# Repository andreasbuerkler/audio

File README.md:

# audio
audio signal processing board

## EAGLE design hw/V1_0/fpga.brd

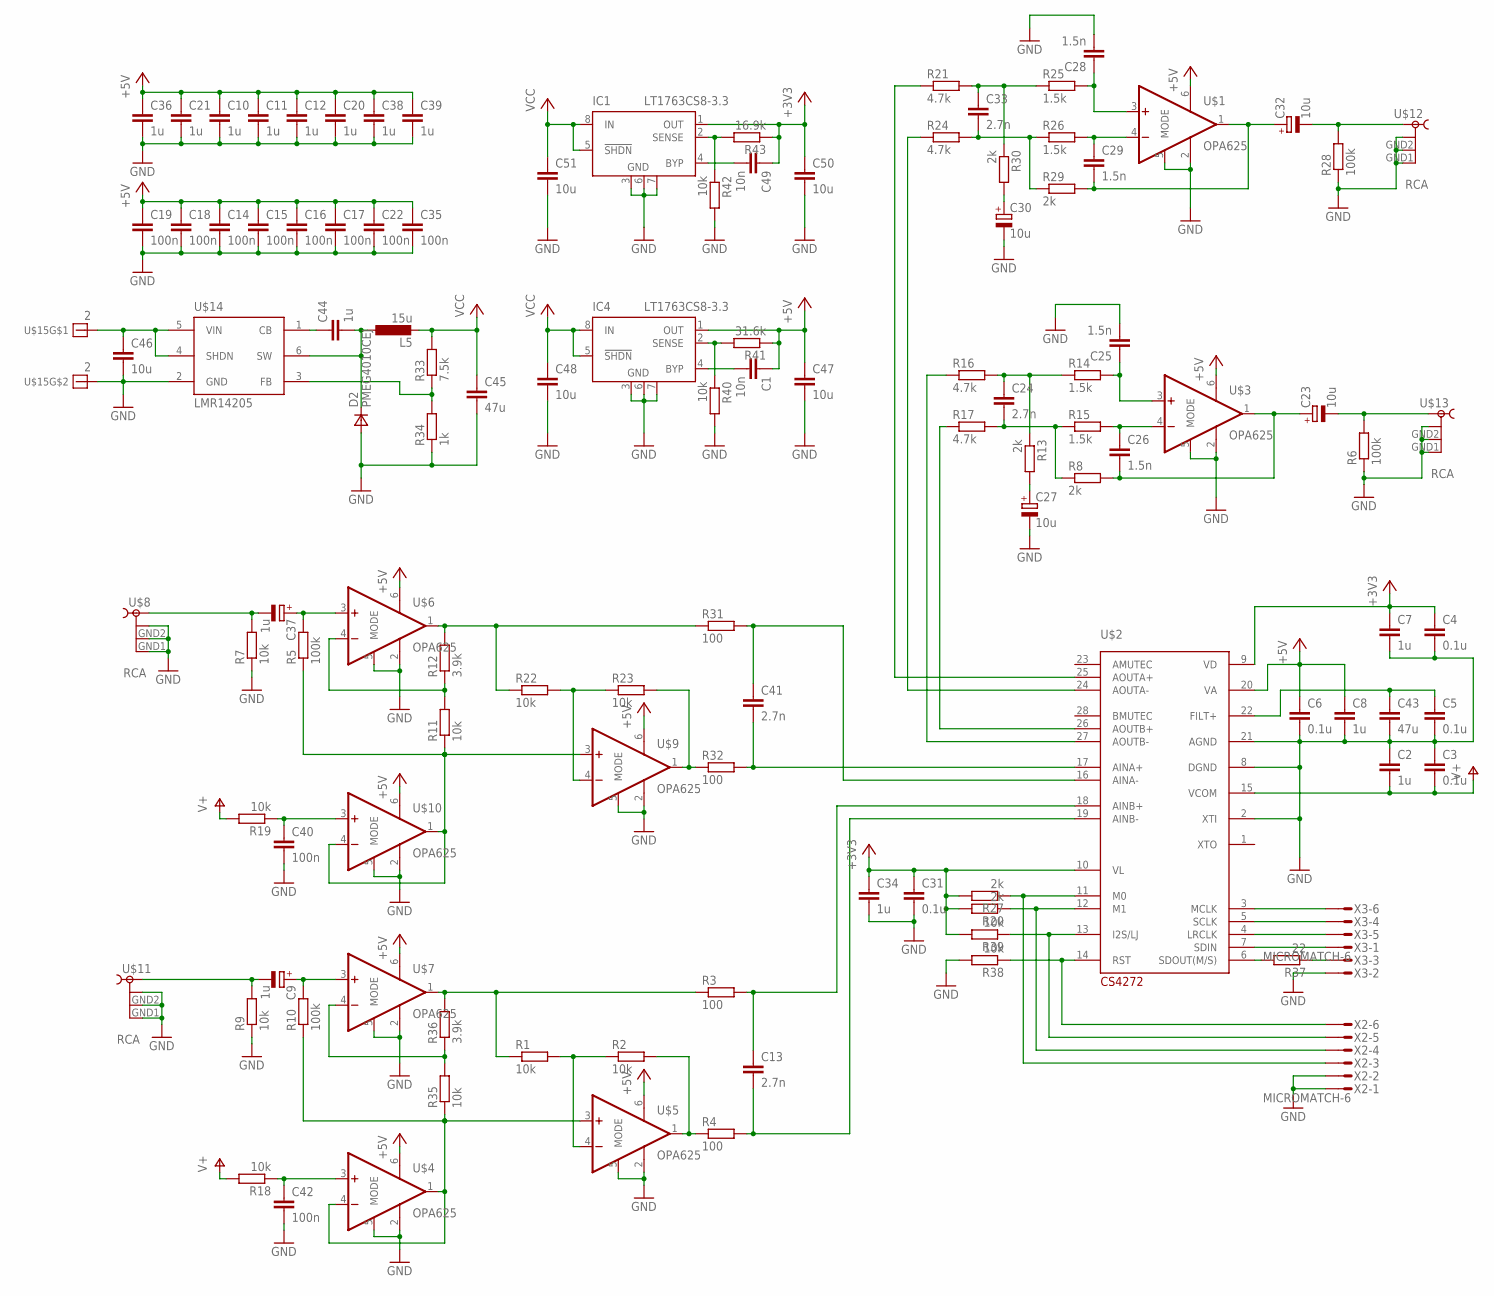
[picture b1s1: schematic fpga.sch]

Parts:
C1, C49: 10n; C0603K
C2, C7, C8, C10, C11, C12, C20, C21, C34, C36, C38, C39, C44: 1u; C0603K
C3, C4, C5, C6, C31: 0.1u; C0603K
C9, C37: 1u; 153CLV-0405
C13, C24, C33, C41: 2.7n; C0603K
C14, C15, C16, C17, C18, C19, C22, C35, C40, C42: 100n; C0603K
C23, C27, C30, C32: 10u; 153CLV-0405
C25, C26, C28, C29: 1.5n; C0603K
C43: 47u; C0805
C45: 47u; C1206
C46: 10u; C0805
C47, C48, C50, C51: 10u; C0603K
D2: PMEG4010CEJ; SOD323
IC1, IC4: LT1763CS8-3.3; SOIC8
L5: 15u; AAA
R1, R2, R7, R9, R11, R18, R19, R22, R23, R35, R38, R39, R40, R42: 10k; R0603
R3, R4, R31, R32: 100; R0603
R5, R6, R10, R28: 100k; R0603
R8, R13, R20, R27, R29, R30: 2k; R0603
R12, R36: 3.9k; R0603
R14, R15, R25, R26: 1.5k; R0603
R16, R17, R21, R24: 4.7k; R0603
R33: 7.5k; R0603
R34: 1k; R0603
R37: 22; R0603
R41: 31.6k; R0603
R43: 16.9k; R0603
U$1, U$3, U$4, U$5, U$6, U$7, U$9, U$10: OPA625; SOT23-6
U$2: CS4272; TSSOP28
U$8, U$11, U$12, U$13: RCA
U$14: LMR14205; TSOT23-6_DDC
U$15: 2
X2, X3: MICROMATCH-6

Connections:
+3V3: C4.1, C7.1, C31.1, C34.1, C49.1, C50.1, IC1.1 (OUT), R20.2, R27.2, R39.2, R43.1, U$2.9 (VD), U$2.10 (VL)
+5V: C1.1, C6.1, C8.1, C10.1, C11.1, C12.1, C14.1, C15.1, C16.1, C17.1, C18.1, C19.1, C20.1, C21.1, C22.1, C35.1, C36.1, C38.1, C39.1, C47.1, IC4.1 (OUT), R41.1, U$1.6 (V+), U$2.20 (VA), U$3.6 (V+), U$4.6 (V+), U$5.6 (V+), U$6.6 (V+), U$7.6 (V+), U$9.6 (V+), U$10.6 (V+)
GND: C2.1, C3.1, C4.2, C5.2, C6.2, C7.2, C8.2, C10.2, C11.2, C12.2, C14.2, C15.2, C16.2, C17.2, C18.2, C19.2, C20.2, C21.2, C22.2, C25.2, C27.-, C28.2, C30.-, C31.2, C34.2, C35.2, C36.2, C38.2, C39.2, C40.2, C42.2, C43.2, C45.2, C46.2, C47.2, C48.2, C50.2, C51.2, D2.2 (A), IC1.3 (GND), IC1.6 (GND), IC1.7 (GND), IC4.3 (GND), IC4.6 (GND), IC4.7 (GND), R6.1, R7.1, R9.1, R28.1, R34.1, R38.2, R40.2, R42.2, U$1.2 (V-), U$1.5 (MODE), U$2.2 (XTI), U$2.8 (DGND), U$2.21 (AGND), U$3.2 (V-), U$3.5 (MODE), U$4.2 (V-), U$4.5 (MODE), U$5.2 (V-), U$5.5 (MODE), U$6.2 (V-), U$6.5 (MODE), U$7.2 (V-), U$7.5 (MODE), U$8.GND1 (4), U$8.GND2 (3), U$8.GND3 (2), U$9.2 (V-), U$9.5 (MODE), U$10.2 (V-), U$10.5 (MODE), U$11.GND1 (4), U$11.GND2 (3), U$11.GND3 (2), U$12.GND1 (4), U$12.GND2 (3), U$12.GND3 (2), U$13.GND1 (4), U$13.GND2 (3), U$13.GND3 (2), U$14.2 (GND), U$15.P$2, X2.1, X2.2, X3.2
unnamed: R10.1, R35.1, U$4.1 (OUT), U$4.4 (-IN), U$5.3 (+IN)
unnamed: C9.+, R10.2, U$7.3 (+IN)
unnamed: R2.2, R4.1, U$5.1 (OUT)
unnamed: C5.1, C43.1, U$2.22 (FILT+)
unnamed: R1.2, R2.1, U$5.4 (-IN)
unnamed: C40.1, R19.1, U$10.3 (+IN)
unnamed: C24.1, R13.1, R14.1, R16.2
unnamed: C13.1, R3.2, U$2.18 (AINB+)
unnamed: C13.2, R4.2, U$2.19 (AINB-)
unnamed: R12.2, R22.1, R31.1, U$6.1 (OUT)
unnamed: C24.2, R8.1, R15.1, R17.2
unnamed: C37.-, R7.2, U$8.S1 (1)
unnamed: C9.-, R9.2, U$11.S1 (1)
unnamed: C25.1, R14.2, U$3.3 (+IN)
unnamed: C26.1, R15.2, U$3.4 (-IN)
unnamed: C23.+, C26.2, R8.2, U$3.1 (OUT)
unnamed: C23.-, R6.2, U$13.S1 (1)
unnamed: C27.+, R13.2
unnamed: C30.+, R30.2
unnamed: C42.1, R18.1, U$4.3 (+IN)
unnamed: IC1.2 (SENSE), R42.1, R43.2
unnamed: R17.1, U$2.26 (AOUTB+)
unnamed: R16.1, U$2.27 (AOUTB-)
unnamed: C49.2, IC1.4 (BYP)
unnamed: R24.1, U$2.24 (AOUTA-)
unnamed: R21.1, U$2.25 (AOUTA+)
unnamed: C33.1, R21.2, R25.1, R30.1
unnamed: R11.2, R12.1, U$6.4 (-IN)
unnamed: C33.2, R24.2, R26.1, R29.1
unnamed: C28.1, R25.2, U$1.3 (+IN)
unnamed: C29.1, R26.2, U$1.4 (-IN)
unnamed: C29.2, C32.+, R29.2, U$1.1 (OUT)
unnamed: R27.1, U$2.11 (M0), X2.3
unnamed: C41.2, R32.2, U$2.17 (AINA+)
unnamed: R1.1, R3.1, R36.2, U$7.1 (OUT)
unnamed: C32.-, R28.2, U$12.S1 (1)
unnamed: R20.1, U$2.12 (M1), X2.4
unnamed: C37.+, R5.2, U$6.3 (+IN)
unnamed: R35.2, R36.1, U$7.4 (-IN)
unnamed: C41.1, R31.2, U$2.16 (AINA-)
unnamed: R5.1, R11.1, U$9.3 (+IN), U$10.1 (OUT), U$10.4 (-IN)
unnamed: C44.1, U$14.1 (CB)
unnamed: R23.2, R32.1, U$9.1 (OUT)
unnamed: C44.2, D2.1 (C), L5.P$1 (1), U$14.6 (SW)
unnamed: R22.2, R23.1, U$9.4 (-IN)
unnamed: R33.1, R34.2, U$14.3 (FB)
unnamed: R38.1, U$2.14 (RST), X2.6
unnamed: R39.1, U$2.13 (I2S/LJ), X2.5
unnamed: U$2.3 (MCLK), X3.6
unnamed: U$2.5 (SCLK), X3.4
unnamed: U$2.4 (LRCLK), X3.5
unnamed: C46.1, U$14.4 (SHDN), U$14.5 (VIN), U$15.P$1
unnamed: U$2.7 (SDIN), X3.1
unnamed: R37.2, U$2.6 (SDOUT(M/S))
unnamed: R37.1, X3.3
unnamed: IC4.2 (SENSE), R40.1, R41.2
unnamed: C1.2, IC4.4 (BYP)
V+: C2.2, C3.2, R18.2, R19.2, U$2.15 (VCOM)
VCC: C45.1, C48.1, C51.1, IC1.5 (!SHDN), IC1.8 (IN), IC4.5 (!SHDN), IC4.8 (IN), L5.P$2 (2), R33.2

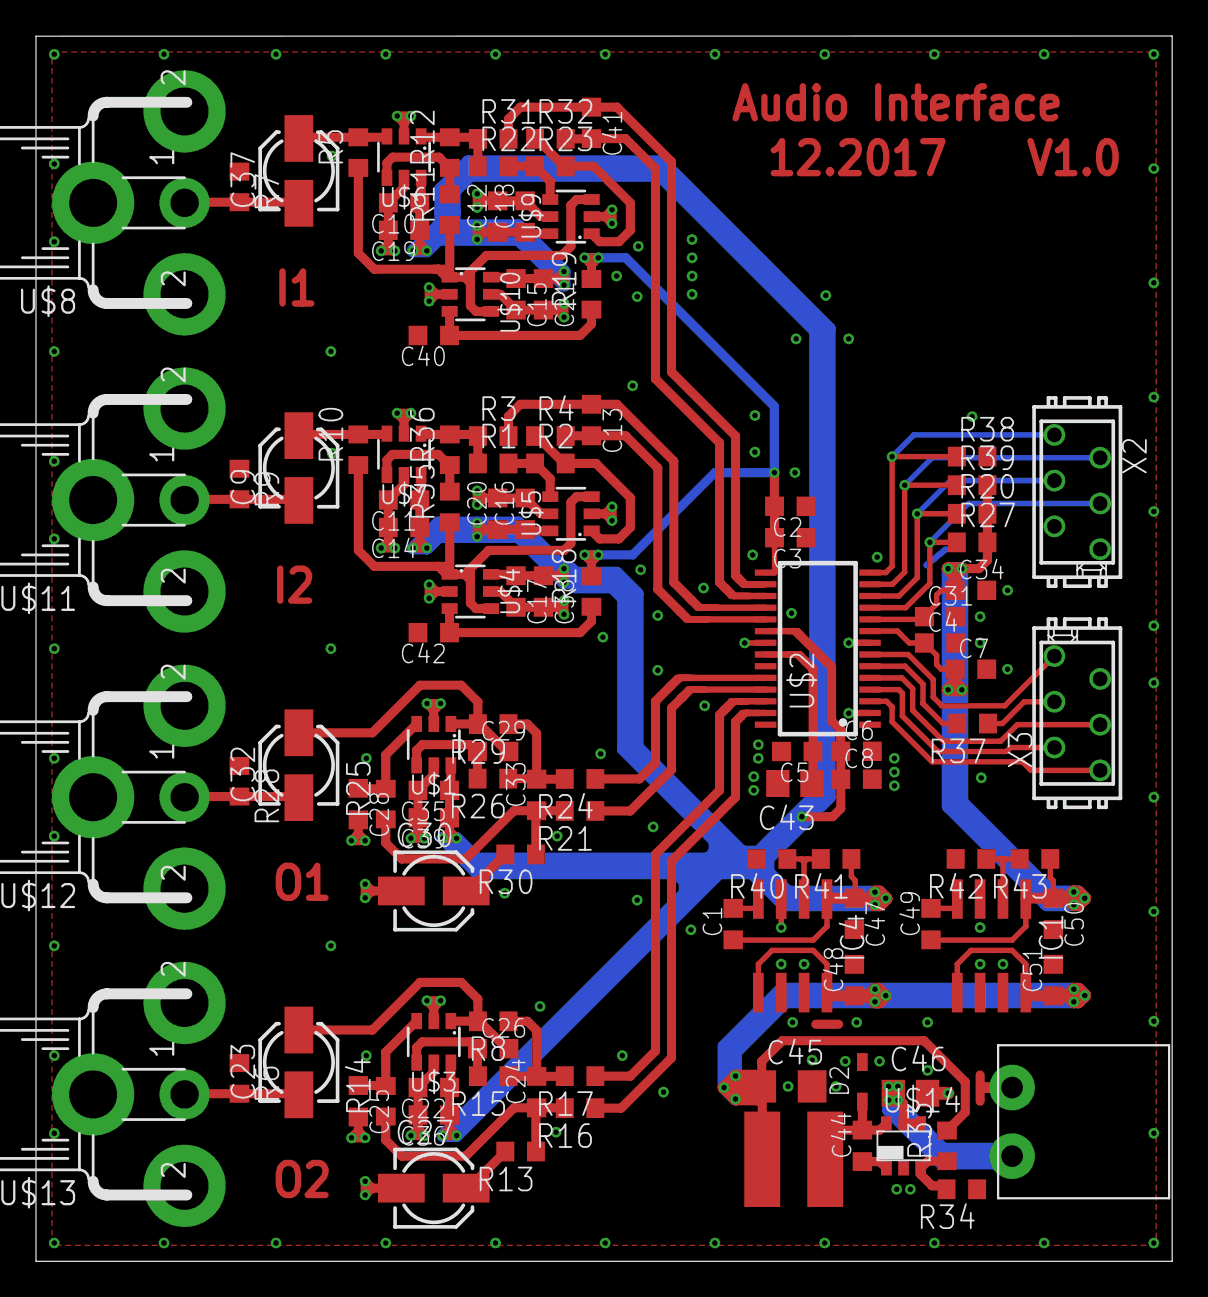
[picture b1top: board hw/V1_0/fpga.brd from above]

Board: 2 copper layers, 63.1 x 68.1 mm, 115 parts (0 on the bottom side), 62 nets.

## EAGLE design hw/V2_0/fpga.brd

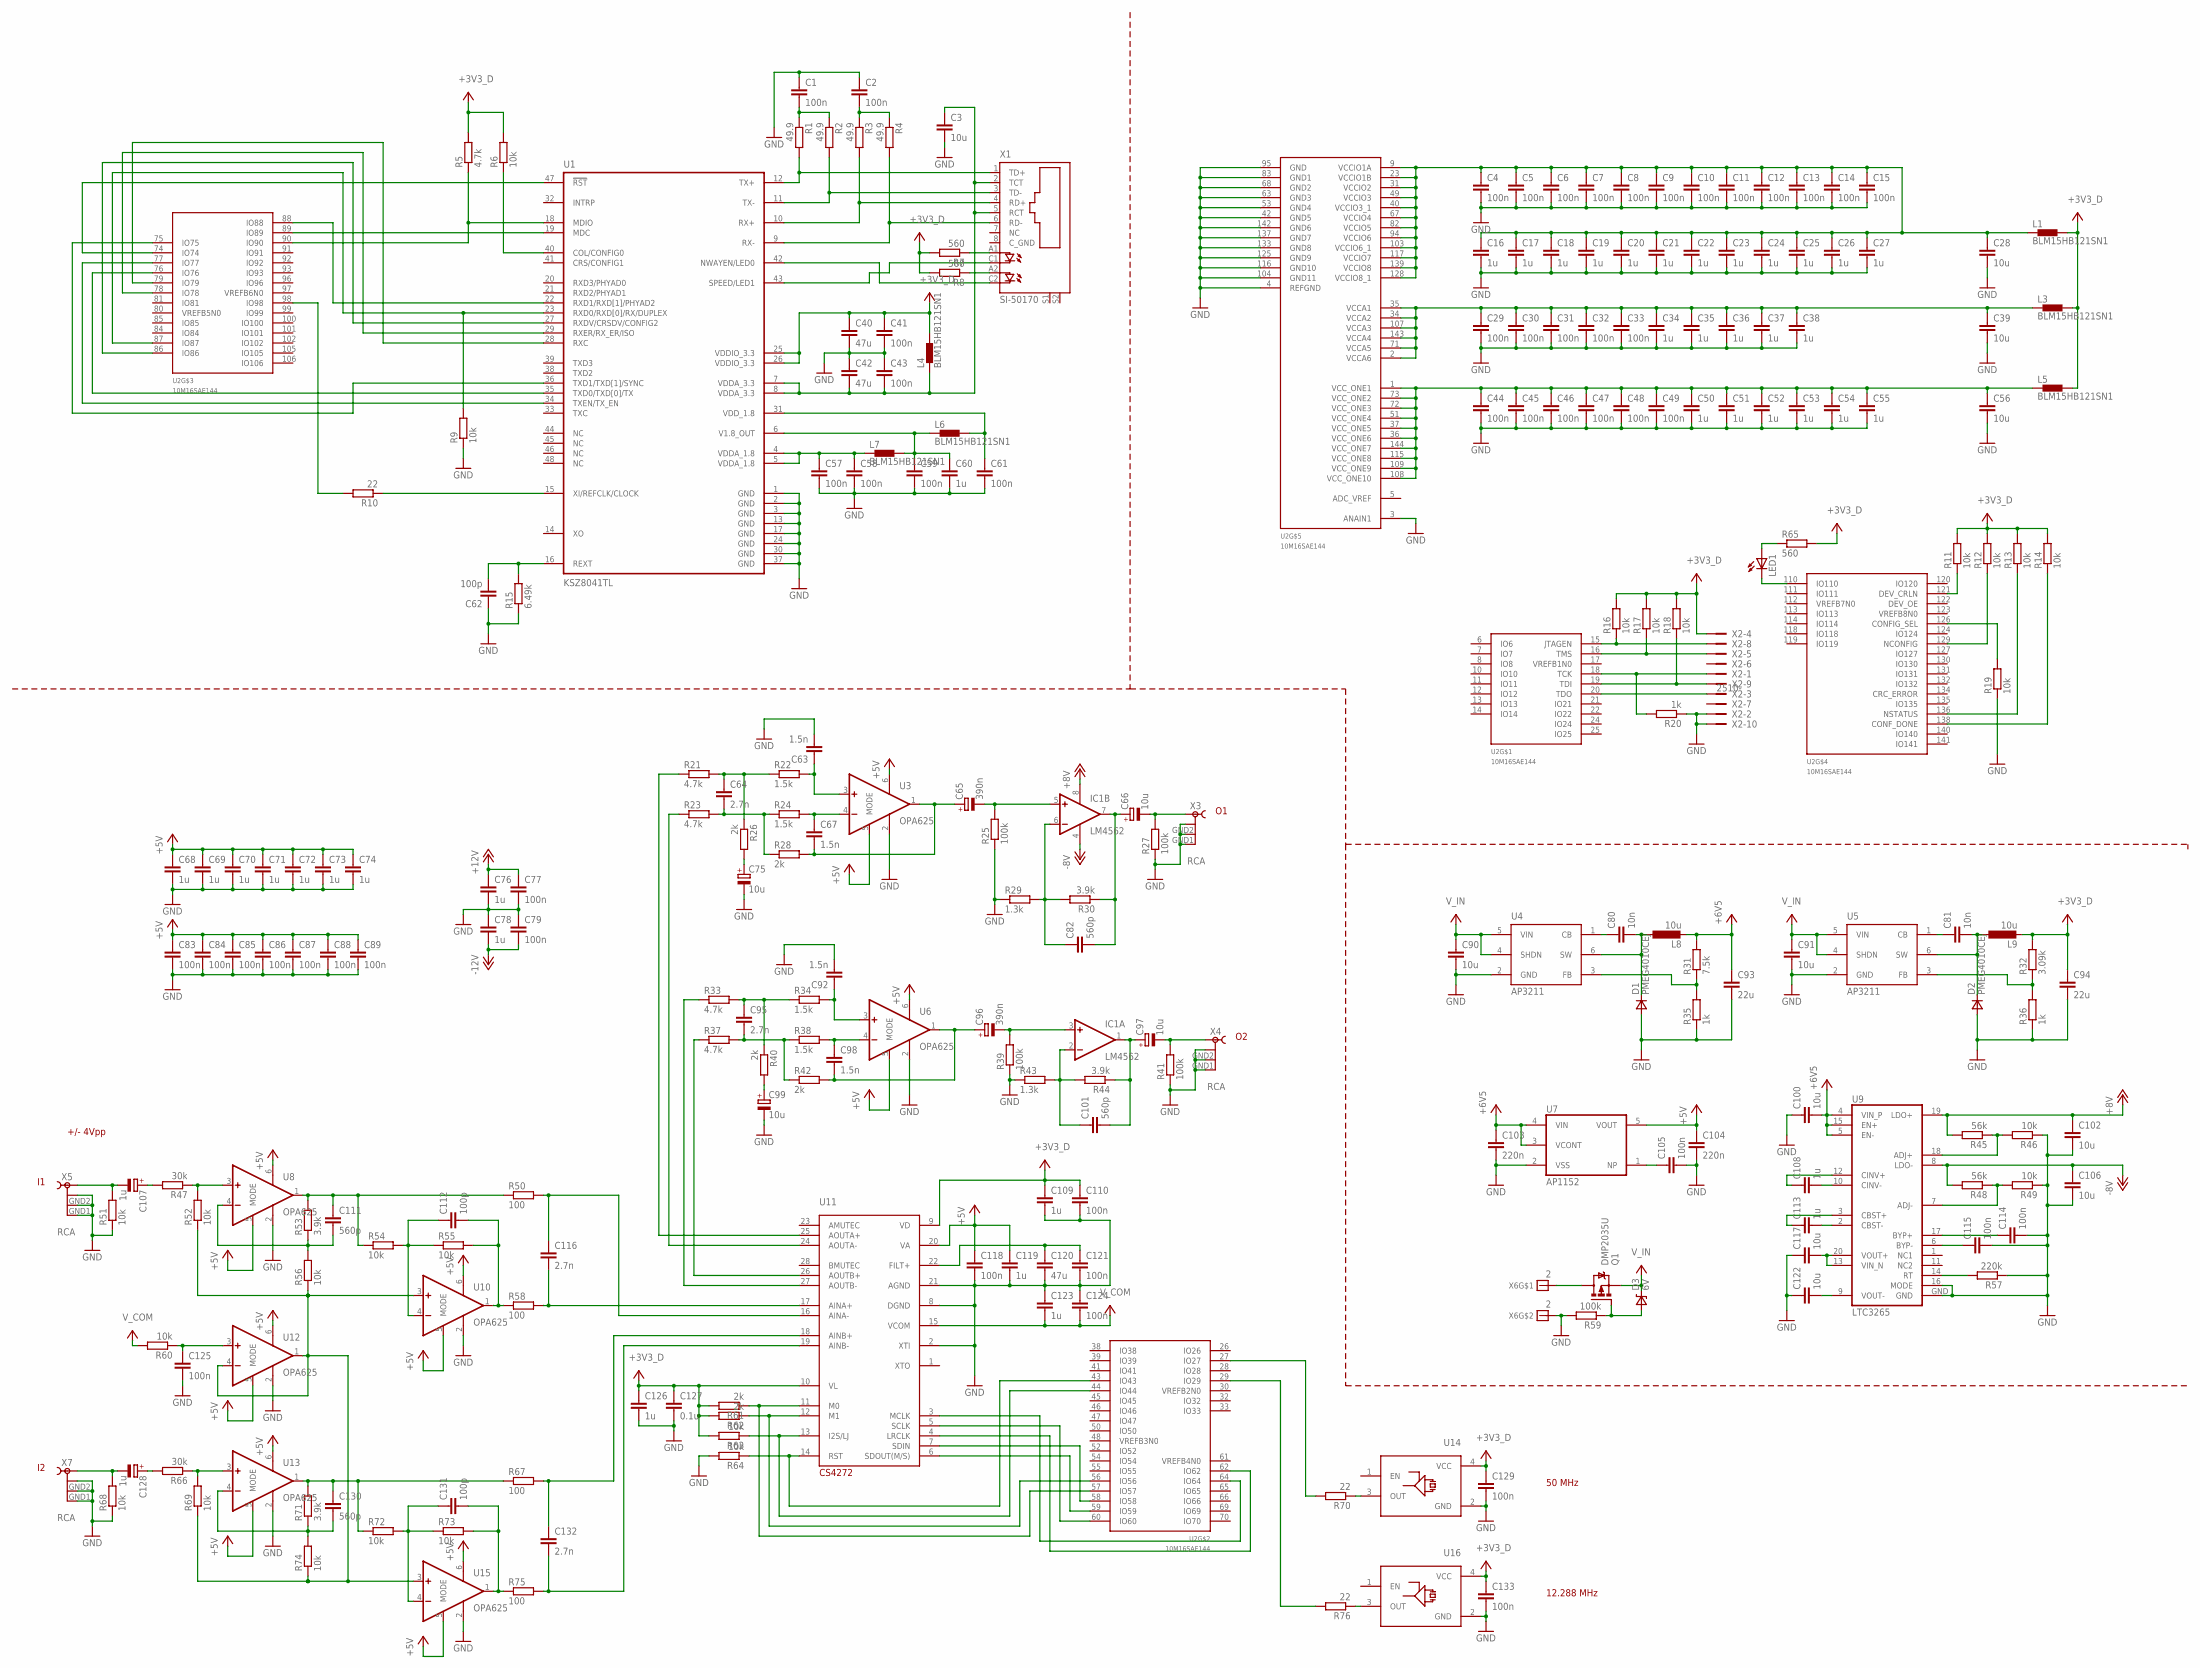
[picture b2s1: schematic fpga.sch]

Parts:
C1, C2, C4, C5, C6, C7, C8, C9, C10, C11, C12, C13, C14, C15, C29, C30, C31, C32, C33, C41, C43, C44, C45, C46, C47, C48, C49, C57, C58, C59, C61, C77, C79, C83, C84, C85, C86, C87, C88, C89, C105, C110, C114, C115, C118, C121, C124, C125, C129, C133: 100n; C0603K
C3, C90, C91: 10u; C0805
C16, C17, C18, C19, C20, C21, C22, C23, C24, C25, C26, C27, C34, C35, C36, C37, C38, C50, C51, C52, C53, C54, C55, C60, C68, C69, C70, C71, C72, C73, C74, C76, C78, C108, C109, C113, C119, C123, C126: 1u; C0603K
C28, C39, C56, C100, C102, C106, C117, C122: 10u; C0603K
C40, C42, C120: 47u; C0805
C62, C112, C131: 100p; C0603K
C63, C67, C92, C98: 1.5n; C0603K
C64, C95, C116, C132: 2.7n; C0603K
C65, C96: 390n; 153CLV-0405
C66, C75, C97, C99: 10u; 153CLV-0405
C80, C81: 10n; C0603K
C82, C101, C111, C130: 560p; C0603K
C93, C94: 22u; C1206
C103, C104: 220n; C0603K
C107, C128: 1u; 153CLV-0405
C127: 0.1u; C0603K
D1, D2: PMEG4010CEJ; SOD323
D3: 6V; SOD323
IC1: LM4562; SO08
L1, L3, L4, L5, L6, L7: BLM15HB121SN1; 0402
L8, L9: 10u; AAA
LED1: LEDCHIPLED_0603; CHIPLED_0603
Q1: DMP2035U; MICRO3
R1, R2, R3, R4: 49.9; R0603
R5, R21, R23, R33, R37: 4.7k; R0603
R6, R9, R11, R12, R13, R14, R16, R17, R18, R19, R46, R49, R51, R52, R54, R55, R56, R60, R63, R64, R68, R69, R72, R73, R74: 10k; R0603
R7, R8, R65: 560; R0603
R10, R70, R76: 22; R0603
R15: 6.49k; R0603
R20, R35, R36: 1k; R0603
R22, R24, R34, R38: 1.5k; R0603
R25, R27, R39, R41, R59: 100k; R0603
R26, R28, R40, R42, R61, R62: 2k; R0603
R29, R43: 1.3k; R0603
R30, R44, R53, R71: 3.9k; R0603
R31: 7.5k; R0603
R32: 3.09k; R0603
R45, R48: 56k; R0603
R47, R66: 30k; R0603
R50, R58, R67, R75: 100; R0603
R57: 220k; R0603
U1: KSZ8041TL; TQFP48
U2: 10M16SAE144; EQFP144
U3, U6, U8, U10, U12, U13, U15: OPA625; SOT23-6
U4, U5: AP3211; TSOT23-6_DDC
U7: AP1152; SOT89-5
U9: LTC3265; TSSOP20_GND
U11: CS4272; TSSOP28
U14: 49.152MHz; OSC
U16: 50MHz; OSC
X1: SI-50170
X2: 2510-; PAK100/2500-10
X3, X4, X5, X7: RCA
X6: 2

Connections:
+3V3_D: C40.1, C41.1, C94.1, C109.1, C110.1, C126.1, C127.1, C129.1, C133.1, L1.2, L3.2, L4.2, L5.2, L9.P$2 (2), R5.2, R6.2, R7.2, R8.2, R11.2, R12.2, R13.2, R14.2, R16.2, R17.2, R18.2, R32.2, R61.2, R62.2, R63.2, R65.2, U1.25 (VDDIO_3.3), U1.26 (VDDIO_3.3), U11.9 (VD), U11.10 (VL), U14.4 (VCC), U16.4 (VCC), X2.4
+5V: C68.1, C69.1, C70.1, C71.1, C72.1, C73.1, C74.1, C83.1, C84.1, C85.1, C86.1, C87.1, C88.1, C89.1, C104.1, C118.1, C119.1, U3.5 (MODE), U3.6 (V+), U6.5 (MODE), U6.6 (V+), U7.5 (VOUT), U8.5 (MODE), U8.6 (V+), U10.5 (MODE), U10.6 (V+), U11.20 (VA), U12.5 (MODE), U12.6 (V+), U13.5 (MODE), U13.6 (V+), U15.5 (MODE), U15.6 (V+)
+12V: C76.1, C77.1, C102.1, IC1.8 (V+), R45.2, U9.19 (LDO+)
-12V: C78.2, C79.2, C106.1, IC1.4 (V-), R48.2, U9.8 (LDO-)
GND: C1.1, C2.1, C3.2, C4.2, C5.2, C6.2, C7.2, C8.2, C9.2, C10.2, C11.2, C12.2, C13.2, C14.2, C15.2, C16.2, C17.2, C18.2, C19.2, C20.2, C21.2, C22.2, C23.2, C24.2, C25.2, C26.2, C27.2, C28.2, C29.2, C30.2, C31.2, C32.2, C33.2, C34.2, C35.2, C36.2, C37.2, C38.2, C39.2, C40.2, C41.2, C42.1, C43.1, C44.2, C45.2, C46.2, C47.2, C48.2, C49.2, C50.2, C51.2, C52.2, C53.2, C54.2, C55.2, C56.2, C57.2, C58.2, C59.2, C60.2, C61.2, C62.1, C63.2, C68.2, C69.2, C70.2, C71.2, C72.2, C73.2, C74.2, C75.-, C76.2, C77.2, C78.1, C79.1, C83.2, C84.2, C85.2, C86.2, C87.2, C88.2, C89.2, C90.2, C91.2, C92.2, C93.2, C94.2, C99.-, C100.1, C102.2, C103.2, C104.2, C105.2, C106.2, C109.2, C110.2, C114.2, C115.2, C117.1, C118.2, C119.2, C120.2, C121.2, C122.1, C123.1, C124.1, C125.2, C126.2, C127.2, C129.2, C133.2, D1.2 (A), D2.2 (A), R9.1, R15.1, R19.1, R20.1, R25.1, R27.1, R29.1, R35.1, R36.1, R39.1, R41.1, R43.1, R46.1, R49.1, R51.1, R57.1, R59.2, R64.2, R68.1, U1.1 (GND), U1.2 (GND), U1.3 (GND), U1.13 (GND), U1.17 (GND), U1.24 (GND), U1.30 (GND), U1.37 (GND), U2.3 (ANAIN1), U2.4 (REFGND), U2.42 (GND5), U2.53 (GND4), U2.63 (GND3), U2.68 (GND2), U2.83 (GND1), U2.95 (GND), U2.104 (GND11), U2.116 (GND10), U2.125 (GND9), U2.133 (GND8), U2.137 (GND7), U2.142 (GND6), U3.2 (V-), U4.2 (GND), U5.2 (GND), U6.2 (V-), U7.2 (VSS), U8.2 (V-), U9.16 (MODE), U9.GND, U10.2 (V-), U11.2 (XTI), U11.8 (DGND), U11.21 (AGND), U12.2 (V-), U13.2 (V-), U14.2 (GND), U15.2 (V-), U16.2 (GND), X2.2, X2.10, X3.GND1 (4), X3.GND2 (3), X3.GND3 (2), X4.GND1 (4), X4.GND2 (3), X4.GND3 (2), X5.GND1 (4), X5.GND2 (3), X5.GND3 (2), X6.P$2, X7.GND1 (4), X7.GND2 (3), X7.GND3 (2)
unnamed: C115.1, U9.6 (BYP-)
unnamed: R66.1, R69.2, U13.3 (+IN)
unnamed: C131.2, R73.2, R75.1, U15.1 (OUT)
unnamed: C120.1, C121.1, U11.22 (FILT+)
unnamed: C131.1, R72.2, R73.1, U15.4 (-IN)
unnamed: C125.1, R60.1, U12.3 (+IN)
unnamed: C95.1, R33.2, R34.1, R40.1
unnamed: C132.1, R67.2, U11.18 (AINB+)
unnamed: C132.2, R75.2, U11.19 (AINB-)
unnamed: C111.1, R50.1, R53.2, R54.1, U8.1 (OUT)
unnamed: C44.1, C45.1, C46.1, C47.1, C48.1, C49.1, C50.1, C51.1, C52.1, C53.1, C54.1, C55.1, C56.1, L5.1, U2.1 (VCC_ONE1), U2.36 (VCC_ONE6), U2.37 (VCC_ONE5), U2.51 (VCC_ONE4), U2.72 (VCC_ONE3), U2.73 (VCC_ONE2), U2.108 (VCC_ONE10), U2.109 (VCC_ONE9), U2.115 (VCC_ONE8), U2.144 (VCC_ONE7)
unnamed: C95.2, R37.2, R38.1, R42.1
unnamed: C107.-, R51.2, X5.S1 (1)
unnamed: C128.-, R68.2, X7.S1 (1)
unnamed: C92.1, R34.2, U6.3 (+IN)
unnamed: C98.1, R38.2, U6.4 (-IN)
unnamed: C96.+, C98.2, R42.2, U6.1 (OUT)
unnamed: C97.-, R41.2, X4.S1 (1)
unnamed: C99.+, R40.2
unnamed: C75.+, R26.2
unnamed: R14.1, U2.138 (CONF_DONE)
unnamed: R70.1, U14.3 (OUT)
unnamed: R13.1, U2.136 (NSTATUS)
unnamed: R37.1, U11.26 (AOUTB+)
unnamed: R33.1, U11.27 (AOUTB-)
unnamed: R12.1, U2.129 (NCONFIG)
unnamed: R23.1, U11.24 (AOUTA-)
unnamed: R21.1, U11.25 (AOUTA+)
unnamed: C64.1, R21.2, R22.1, R26.1
unnamed: C111.2, R53.1, R56.2, U8.4 (-IN)
unnamed: R16.1, U2.15 (JTAGEN), X2.8
unnamed: C64.2, R23.2, R24.1, R28.1
unnamed: C63.1, R22.2, U3.3 (+IN)
unnamed: C67.1, R24.2, U3.4 (-IN)
unnamed: C65.+, C67.2, R28.2, U3.1 (OUT)
unnamed: R61.1, U2.57 (IO57), U11.11 (M0)
unnamed: C116.2, R58.2, U11.17 (AINA+)
unnamed: C130.1, R67.1, R71.2, R72.1, U13.1 (OUT)
unnamed: C65.-, IC1.5 (+IN), R25.2
unnamed: R62.1, U2.56 (IO56), U11.12 (M1)
unnamed: R47.1, R52.2, U8.3 (+IN)
unnamed: C130.2, R71.1, R74.2, U13.4 (-IN)
unnamed: C116.1, R50.2, U11.16 (AINA-)
unnamed: R52.1, R56.1, R69.1, R74.1, U10.3 (+IN), U12.1 (OUT), U12.4 (-IN), U15.3 (+IN)
unnamed: C80.1, U4.1 (CB)
unnamed: C112.2, R55.2, R58.1, U10.1 (OUT)
unnamed: C80.2, D1.1 (C), L8.P$1 (1), U4.6 (SW)
unnamed: C112.1, R54.2, R55.1, U10.4 (-IN)
unnamed: C81.1, U5.1 (CB)
unnamed: R31.1, R35.2, U4.3 (FB)
unnamed: R64.1, U2.43 (IO43), U11.14 (RST)
unnamed: R63.1, U2.44 (IO44), U11.13 (I2S/LJ)
unnamed: U2.64 (IO64), U11.3 (MCLK)
unnamed: U2.60 (IO60), U11.5 (SCLK)
unnamed: U2.62 (IO62), U11.4 (LRCLK)
unnamed: R76.1, U16.3 (OUT)
unnamed: U2.58 (IO58), U11.7 (SDIN)
unnamed: U2.59 (IO59), U11.6 (SDOUT(M/S))
unnamed: U1.42 (NWAYEN/LED0), X1.C2 (C1)
unnamed: C81.2, D2.1 (C), L9.P$1 (1), U5.6 (SW)
unnamed: R70.2, U2.27 (IO27)
unnamed: R32.1, R36.2, U5.3 (FB)
unnamed: R20.2, U2.18 (TCK), X2.1
unnamed: R19.2, U2.126 (CONFIG_SEL)
unnamed: C29.1, C30.1, C31.1, C32.1, C33.1, C34.1, C35.1, C36.1, C37.1, C38.1, C39.1, L3.1, U2.2 (VCCA6), U2.34 (VCCA2), U2.35 (VCCA1), U2.71 (VCCA5), U2.107 (VCCA3), U2.143 (VCCA4)
unnamed: R17.1, U2.16 (TMS), X2.5
unnamed: R18.1, U2.19 (TDI), X2.9
unnamed: C4.1, C5.1, C6.1, C7.1, C8.1, C9.1, C10.1, C11.1, C12.1, C13.1, C14.1, C15.1, C16.1, C17.1, C18.1, C19.1, C20.1, C21.1, C22.1, C23.1, C24.1, C25.1, C26.1, C27.1, C28.1, L1.1, U2.9 (VCCIO1A), U2.23 (VCCIO1B), U2.31 (VCCIO2), U2.40 (VCCIO3_1), U2.49 (VCCIO3), U2.67 (VCCIO4), U2.82 (VCCIO5), U2.94 (VCCIO6), U2.103 (VCCIO6_1), U2.117 (VCCIO7), U2.128 (VCCIO8_1), U2.139 (VCCIO8)
unnamed: U2.20 (TDO), X2.3
unnamed: Q1.3 (D), X6.P$1
unnamed: U1.43 (SPEED/LED1), X1.C1 (C)
unnamed: C57.1, C58.1, L7.1, U1.4 (VDDA_1.8), U1.5 (VDDA_1.8)
unnamed: LED1.C, U2.110 (IO110)
unnamed: C59.1, C60.1, L6.1, L7.2, U1.6 (V1.8_OUT)
unnamed: R7.1, X1.A1 (A)
unnamed: C61.1, L6.2, U1.31 (VDD_1.8)
unnamed: R8.1, X1.A2 (A1)
unnamed: R2.2, U1.11 (TX-), X1.3 (TD-)
unnamed: R1.2, U1.12 (TX+), X1.1 (TD+)
unnamed: R3.2, U1.10 (RX+), X1.4 (RD+)
unnamed: R4.2, U1.9 (RX-), X1.6 (RD-)
unnamed: C1.2, R1.1, R2.1
unnamed: C2.2, R3.1, R4.1
unnamed: LED1.A, R65.1
unnamed: C3.1, C42.2, C43.2, L4.1, U1.7 (VDDA_3.3), U1.8 (VDDA_3.3), X1.2 (TCT), X1.5 (RCT)
unnamed: D3.2 (A), Q1.1 (G), R59.1
unnamed: R10.1, U1.15 (XI/REFCLK/CLOCK)
unnamed: U1.34 (TXEN/TX_EN), U2.77 (IO77)
unnamed: U1.35 (TXD0/TXD[0]/TX), U2.76 (IO76)
unnamed: U1.36 (TXD1/TXD[1]/SYNC), U2.75 (IO75)
unnamed: U1.22 (RXD1/RXD[1]/PHYAD2), U2.88 (IO88)
unnamed: R9.2, U1.23 (RXD0/RXD[0]/RX/DUPLEX), U2.87 (IO87)
unnamed: U1.27 (RXDV/CRSDV/CONFIG2), U2.86 (IO86)
unnamed: U1.29 (RXER/RX_ER/ISO), U2.78 (IO78)
unnamed: R10.2, U2.98 (IO98)
unnamed: R6.1, U1.40 (COL/CONFIG0)
unnamed: U1.19 (MDC), U2.89 (IO89)
unnamed: R5.1, U1.18 (MDIO), U2.90 (IO90)
unnamed: U1.28 (RXC), U2.79 (IO79)
unnamed: U1.47 (!RST), U2.74 (IO74)
unnamed: C62.2, R15.2, U1.16 (REXT)
unnamed: R76.2, U2.29 (IO29)
unnamed: C96.-, IC1.3 (+IN), R39.2
unnamed: C82.1, IC1.6 (-IN), R29.2, R30.2
unnamed: C66.+, C82.2, IC1.7 (OUT), R30.1
unnamed: C66.-, R27.2, X3.S1 (1)
unnamed: C101.1, IC1.2 (-IN), R43.2, R44.2
unnamed: C97.+, C101.2, IC1.1 (OUT), R44.1
unnamed: R45.1, R46.2, U9.18 (ADJ+)
unnamed: C113.2, U9.2 (CBST-)
unnamed: C113.1, U9.3 (CBST+)
unnamed: C108.2, U9.10 (CINV-)
unnamed: C108.1, U9.12 (CINV+)
unnamed: C105.1, U7.1 (NP)
unnamed: C122.2, U9.9 (VOUT-)
unnamed: C117.2, U9.13 (VIN_N), U9.20 (VOUT+)
unnamed: R57.2, U9.14 (RT)
unnamed: C107.+, R47.2
unnamed: C114.1, U9.17 (BYP+)
unnamed: R48.1, R49.2, U9.7 (ADJ-)
unnamed: C128.+, R66.2
unnamed: R11.1, U2.121 (DEV_CRLN)
VCC: C93.1, C100.2, C103.1, L8.P$2 (2), R31.2, U7.3 (VCONT), U7.4 (VIN), U9.4 (VIN_P), U9.5 (EN-), U9.15 (EN+)
V_COM: C123.2, C124.2, R60.2, U11.15 (VCOM)
V_IN: C90.1, C91.1, D3.1 (C), Q1.2 (S), U4.4 (SHDN), U4.5 (VIN), U5.4 (SHDN), U5.5 (VIN)

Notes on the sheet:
50 MHz
12.288 MHz
+/- 4Vpp

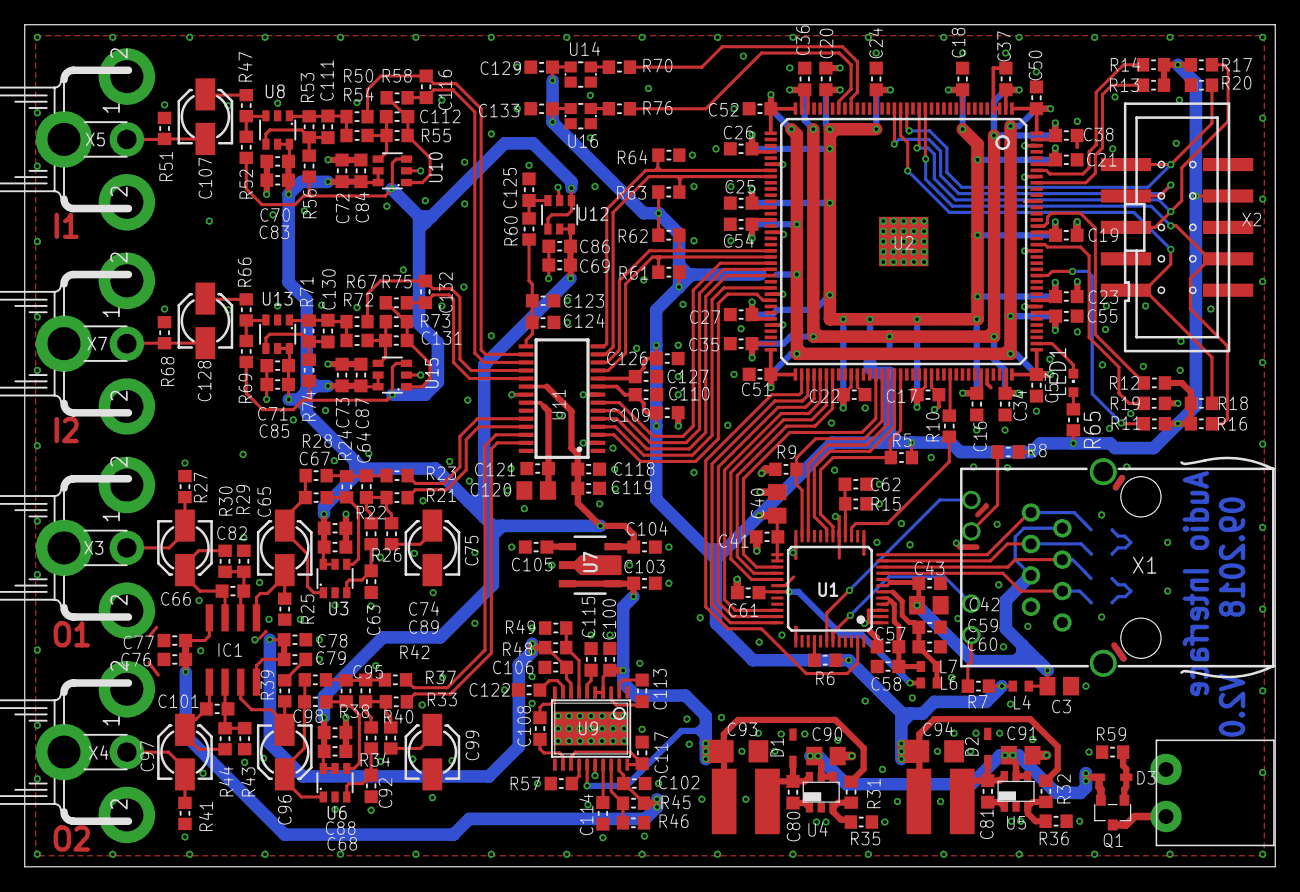
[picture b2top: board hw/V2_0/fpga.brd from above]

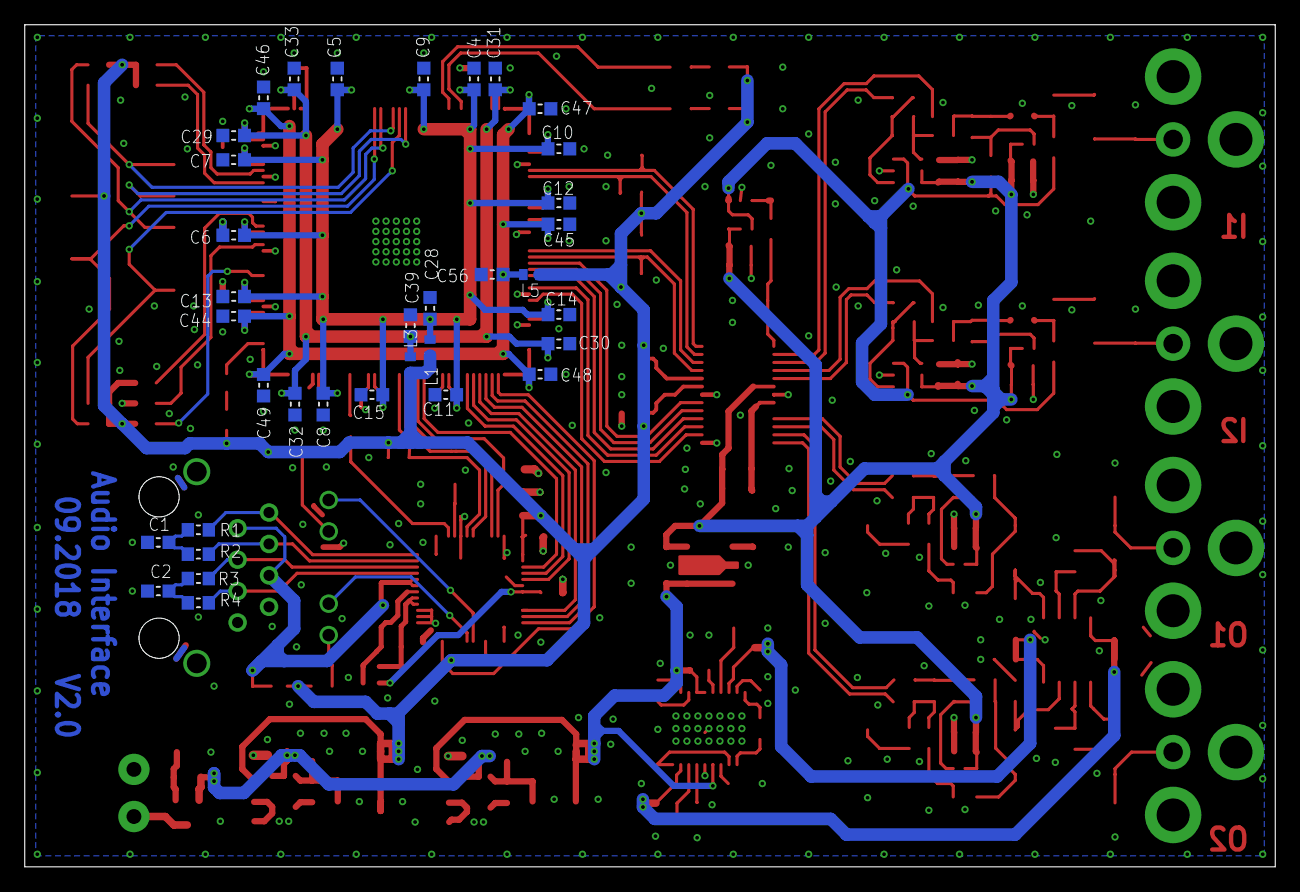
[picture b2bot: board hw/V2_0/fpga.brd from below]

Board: 2 copper layers, 101.1 x 68.1 mm, 246 parts (35 on the bottom side), 130 nets.

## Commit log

2018-10-08 Existing files added
2018-10-19 ETH CRC calculation added
2018-10-20 Ethernet padding generator added
2018-10-21 FIFO added
2018-10-27 FIFO updated
2018-10-28 Some bugfixes in FCS calculation und minor updates / FIFO updated / ETH mac top level file added
2018-10-28 RMII interface added / minor changes in FCS and MAC
2018-11-11 ETH stuff added (only ARP response working) / testbench compile script added / Quartus project and timing constraints updated / minor bugfix in ETH MAC
2018-11-17 ARP table removed / new concept for packet response
2018-11-25 ICMP echo block added
2018-12-02 IP block added / ping reply is now working
2018-12-09 Some bugfixes in eth_processing / testbench of eth_subsystem renamed / testbench compile script updated
2018-12-16 eth testbench updated and some bugfixes
2018-12-23 First part of control software added
2018-12-24 udp block added
2018-12-26 ip checksum fixed /udp packet receive now functional
2018-12-27 Software updated
2018-12-29 control bus master and registerbank added
2018-12-29 registerbank added to top level file / some bugfixes
2019-01-01 register access improved
2019-01-06 meter widget and widget updater added
2019-01-13 meter updated and to project added
2019-01-20 Software updated: register dummy interface added
2019-01-27 Software updated (first version of slider added)
2019-01-30 Sostware updated: stylesheet added and widget appearance changed
2019-02-03 sw meter and slider updated
2019-02-03 fader renamed
2019-02-03 Fader added to register updater
2019-02-23 fader added
2019-03-09 Convolution block added
2019-03-09 convolution test bench updated and fixed / pll added / convolution added to top level
2019-03-24 sinus generator added
2019-04-13 overflow protection added to convolution unit / sinus generator updated with cosinus output
2019-10-27 PoE HW added
2020-01-04 I2C master added
2020-01-26 MDIO debug and interconnect logic added
2020-01-26 design files for FPGA board added
2020-01-26 Testbench compile script updated
2020-01-29 Some bugfixes in I2C master
2020-01-29 New software project started
2020-02-09 Clock crossing FIFO added
2020-03-08 LCD controller added
2020-04-04 hyper ram controller added
2020-04-05 LCD quartus project and top level file added
2020-04-09 Timing constraints for hyper ram added
2020-04-11 hyper ram controller updated
2020-04-14 software updated for firmware debugging
2020-04-26 burst write added in software / memory test updated
2020-04-26 Timing constraints updated / global and eth phy reset added / minor fixes
2020-05-01 LCD controller added to project for first tests on hw
2020-05-01 Timing constraints for lcd added
2020-05-02 Interconnect updated to support bursts
2020-05-10 bursts added for entire control bus
2020-05-16 hyper ram controller testbench updated / some fixes in eth_ctrl for burst transfers
2020-05-17 Software changed to work with updated firmware (2 byte data length)
2020-05-18 Interconnect for multiple masters added
2020-05-18 files for lcd board added
2020-05-20 master interconnect testbench added / some bugfixes in master interconnect / master interconnect added to top level file
2020-05-23 master interconnect testbench updated + bugfix
2020-05-30 Bugfix in master interconnect
2020-06-14 LCD controller updated/fixed and connected in top level
2020-07-08 Text write functionality added in software
2020-08-02 sw: image background and speed bar added
2020-08-02 lcd controller updated to support double buffer / recover when DMA is too slow
2020-08-02 control bus interconnect logic improved
2020-08-03 interconnect testbench added / bugfix in slave_interconnect
2020-08-23 Software updated to display real data
2020-09-26 sw updated (splash screen added / image flipped / cleanup)
2020-09-27 added ability to change background
2020-10-04 Sw cleanup and some bugfixes
2020-11-14 Sleep removed / speed bar color change added

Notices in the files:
parts and their libraries:
micrel_phy: Copyright (C) 2008, Bob Starr
torex: Copyright (C) 2015, Bob Starr
